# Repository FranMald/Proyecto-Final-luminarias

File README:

Prueba de archivo readme sadfasdasd

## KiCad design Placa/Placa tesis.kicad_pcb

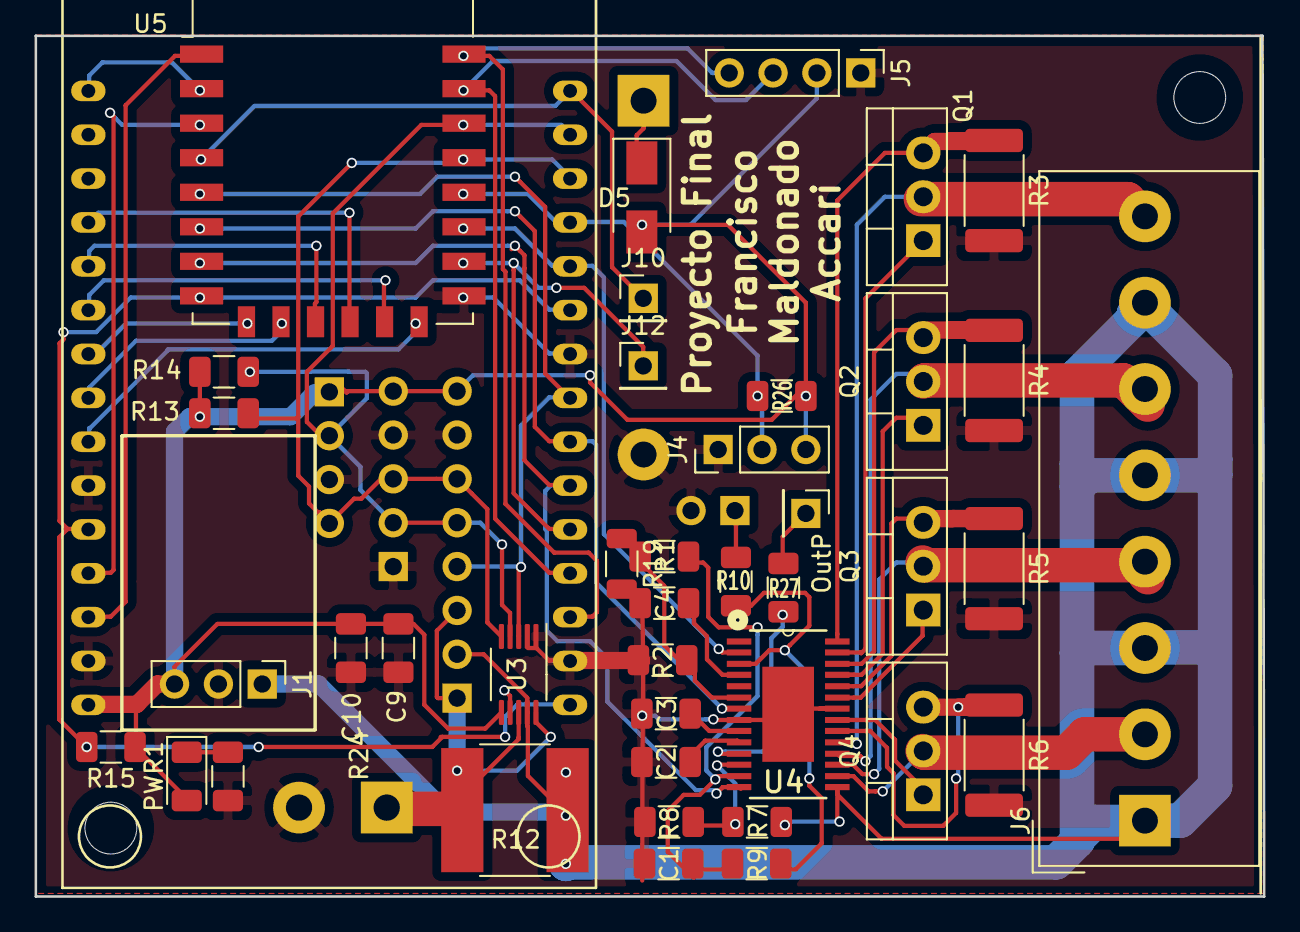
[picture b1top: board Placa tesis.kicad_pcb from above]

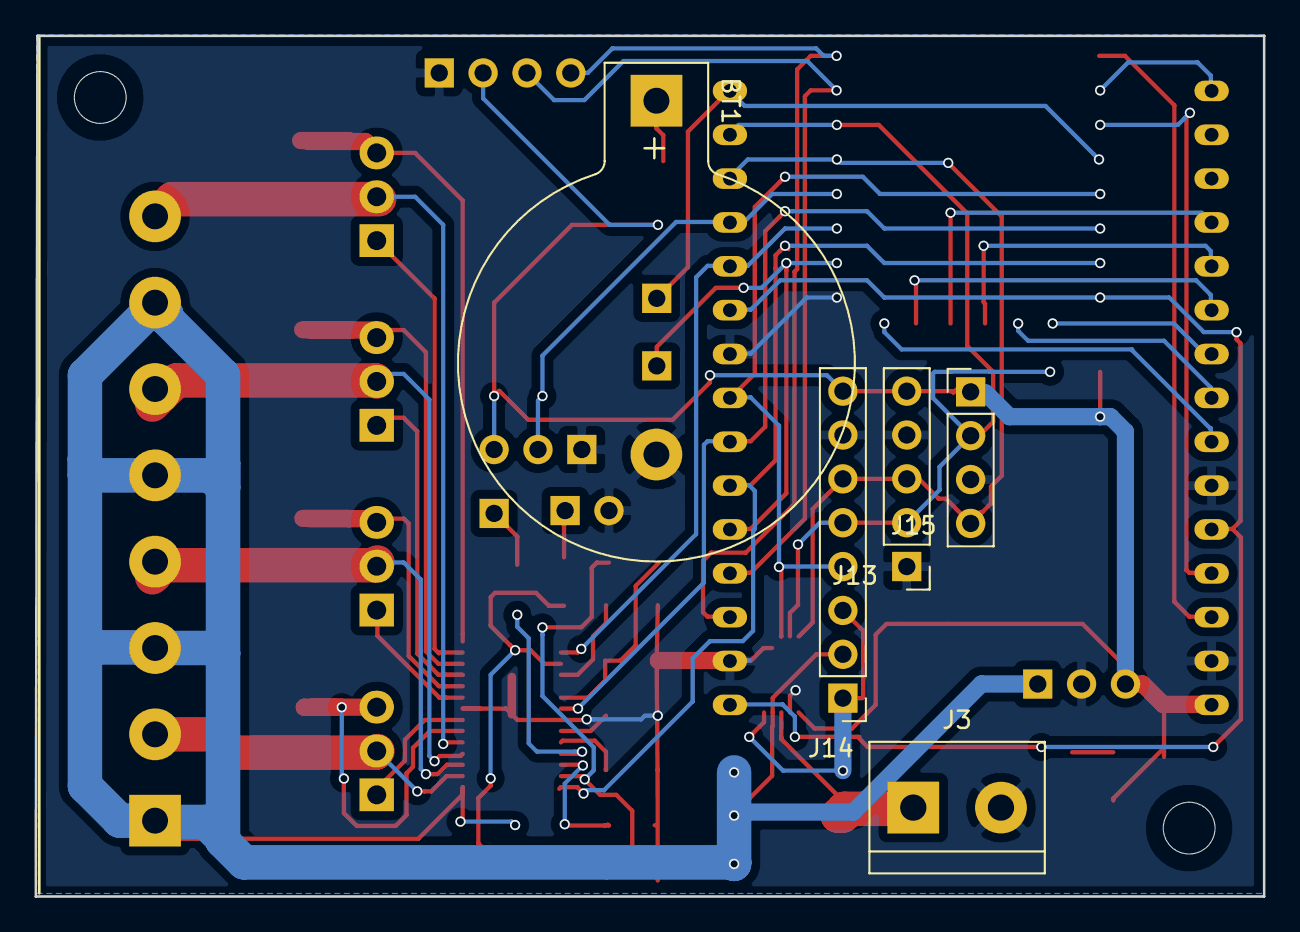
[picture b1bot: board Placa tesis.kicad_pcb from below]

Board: 2 copper layers, 71.1 x 49.9 mm, 47 parts (5 on the bottom side), 48 nets.

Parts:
BT1: Battery_Cell; BatteryHolder_Keystone_103_1x20mm
C1, C2, C4: 1u; C_1206_3216Metric
C3: 2.2n; C_1206_3216Metric
C9: 4.7u; C_1206_3216Metric
C10: 100n; C_1206_3216Metric
D5: DIODE; D_SMA
J1: OKI-78SR; Pin_Header_Straight_1x03_Pitch2.54mm
J3: FUENTE; TerminalBlock_bornier-2_P5.08mm
J4: DHT11; PinHeader_1x03_P2.54mm_Vertical
J5: COMM; PinHeader_1x04_P2.54mm_Vertical
J6: Conn_01x08; Altech_AK300_1x08_P5.00mm_45-Degree
J10, J12: Conn_01x01; PinHeader_1x01_P2.54mm_Vertical
J13: BH1750; PinHeader_1x05_P2.54mm_Vertical
J14: INA226; PinHeader_1x08_P2.54mm_Vertical
J15: Conn_01x04; PinHeader_1x04_P2.54mm_Vertical
OutP: Pin_Header_Straight_1x01_Pitch2.54mm
PWR1: LED; LED_1206_3216Metric
Q1, Q2, Q3, Q4: Q_NMOS_GDS; TO-220-3_Vertical
R1, R7, R19: 10k; R_1206_3216Metric
R2, R26: 4.7k; R_1206_3216Metric
R3, R4, R5, R6: 0.2; R_2512_6332Metric
R8: 1.5k; R_1206_3216Metric
R9, R10, R27: R; R_1206_3216Metric
R12: 270; R_2816
R13, R14: 10K; R_1206_3216Metric
R15: 0.001; R_1206_3216Metric
R24: 270; R_1206_3216Metric
TH1: Thermistor_NTC; Pin_Header_Angled_1x02_Pitch2.54mm
U2: Nodemcuv_3; DIP-30_1098_ELL
U3: INA226; VSSOP-10_3x3mm_P0.5mm
U4: LM3464AMH_NOPB; SOP65P640X110-29N
U5: ESP-12E

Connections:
A0: U2.1, U5.2
ALARM: J14.4, U2.23, U3.3, U5.5
D0: J10.1, U2.30, U5.4
D1: J13.2, J14.5, J15.2, R14.1, U2.29, U3.4, U5.20
D2: J13.3, J14.6, J15.4, R13.1, U2.28, U3.5, U5.19
D3: J4.2, R26.2, U2.27, U5.18
D4: U2.26, U4.2, U5.17
D6: U2.22, U4.7, U5.6
D7: U2.21, U4.14, U5.7
D8: J12.1, R19.1, U2.20, U5.16
DR1: J6.8, Q1.2, U4.19
DR2: J6.6, Q2.2, U4.18
DR3: J6.4, Q3.2, U4.17
DR4: J6.2, Q4.2, U4.16
EN_esp: U2.12, U5.3
GD1: Q1.1, U4.27
GD2: Q2.1, U4.25
GD3: Q3.1, U4.23
GD4: Q4.1, U4.21
GND: BT1.2, C1.2, C2.2, C3.2, C4.2, C9.2, C10.2, J1.2, J3.2, J4.1, J5.1, J13.1, J13.4, J14.7, J15.3, R2.2, R3.2, R4.2, R5.2, R6.2, R8.2, R19.2, R24.1, TH1.2, U2.10, U2.14, U2.17, U2.24, U3.1, U3.2, U3.7, U4.8, U4.22, U5.15
unnamed: BT1.1, D5.1
unnamed: C2.1, U4.10
unnamed: C3.1, U4.9
unnamed: C4.1, U4.4
unnamed: PWR1.1, R24.2
unnamed: R1.2, R2.1, U4.6
unnamed: R7.2, R8.1, U4.12
unnamed: R9.2, R10.1, U4.3
unnamed: R27.2, U4.11
OutP: OutP.1, R27.1
RST_esp: U2.13, U5.1
RX: J5.3, U2.19, U5.21
S0: U2.8, U5.10
S1: U2.6, U5.13
S2: U2.5, U5.11
S3: U2.4, U5.12
SC: U2.7, U5.9
SE1: Q1.3, R3.1, U4.28
SE2: Q2.3, R4.1, U4.26
SE3: Q3.3, R5.1, U4.24
SE4: Q4.3, R6.1, U4.20
SK: U2.9, U5.14
THR: R10.2, TH1.1
TX: J5.4, U2.18, U5.22
V5: C9.1, C10.1, D5.2, J1.3, J4.3, J5.2, J13.5, J14.8, J15.1, PWR1.2, R13.2, R14.2, R15.1, R15.2, R26.1, U2.11, U2.15, U2.16, U2.25, U3.6, U5.8
VccLED: C1.1, R1.1, R9.1, U4.13
Vin: J1.1, J6.1, J6.3, J6.5, J6.7, J14.2, R7.1, R12.1, U3.9, U4.15
VinS: J3.1, J14.1, J14.3, R12.2, U3.8, U3.10

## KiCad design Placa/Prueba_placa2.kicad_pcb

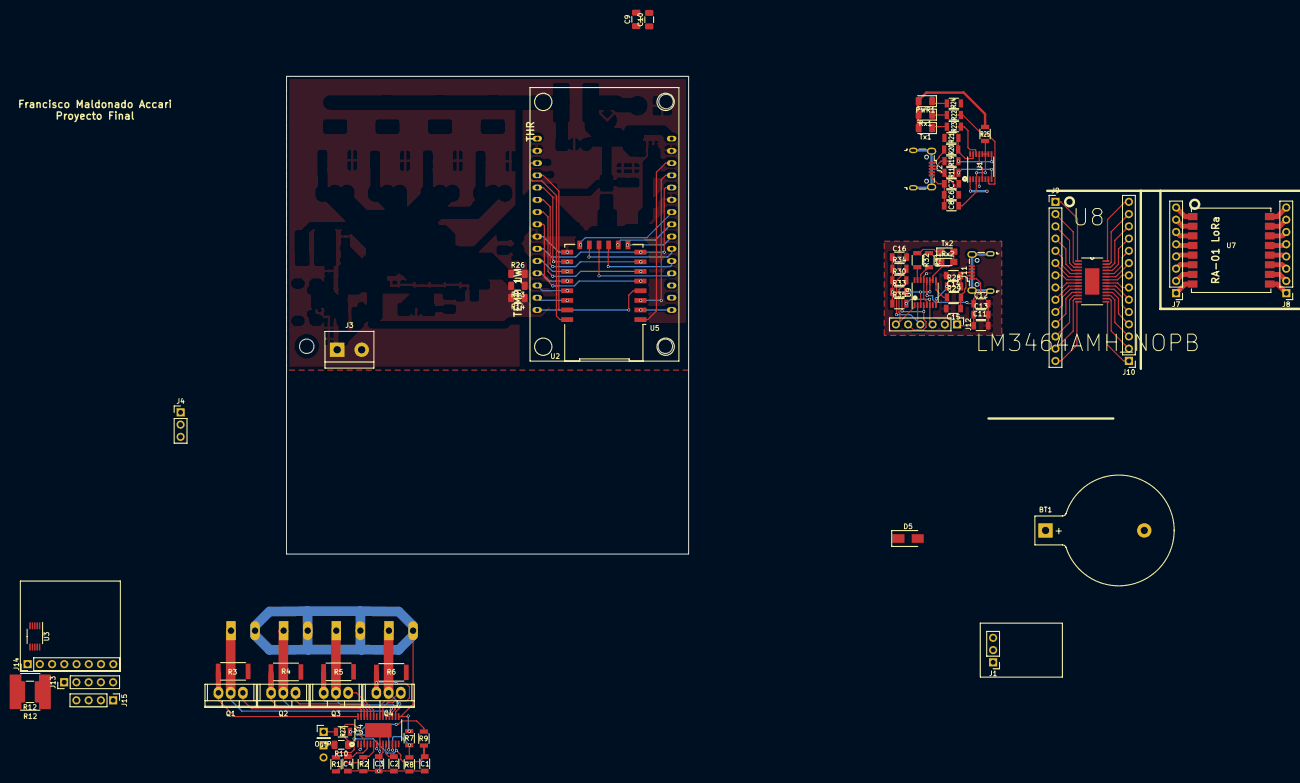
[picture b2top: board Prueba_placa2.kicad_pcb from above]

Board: 2 copper layers, 85 parts (0 on the bottom side), 119 nets.

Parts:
BT1: Battery_Cell; BatteryHolder_Keystone_103_1x20mm
C1, C13: 10n; C_1206
C2, C3, C4: C; C_1206
C6, C7, C14, C15: 47p; C_1206
C8, C12, C16: 100n; C_1206
C9: 4.7u; C_1206_3216Metric
C10: 100n; C_1206_3216Metric
C11: 4.7u; C_1206
D1, D2, D4: LED; TerminalBlock_Altech_AK300-2_P5.00mm
D3: LED; TerminalBlock_Altech_AK300-2_P5.00mmnosilk
D5: DIODE; D_SMA
J1: Conn_01x03; Pin_Header_Straight_1x03_Pitch2.54mm
J2, J11: USB_B_Micro; USB_Micro-B_Wuerth-629105150521
J3: Conn_01x02; TerminalBlock_bornier-2_P5.08mm
J4: Conn_01x03; PinHeader_1x03_P2.54mm_Vertical
J7, J8: Conn_01x08; Pin_Header_Straight_1x08_Pitch2.54mm
J9, J10: Conn_01x14; Pin_Header_Straight_1x14_Pitch2.54mm
J12: Conn_01x06; Pin_Header_Straight_1x06_Pitch2.54mm
J13: Conn_01x05; PinHeader_1x05_P2.54mm_Vertical
J14: Conn_01x08; PinHeader_1x08_P2.54mm_Vertical
J15: Conn_01x04; PinHeader_1x04_P2.54mm_Vertical
OutP: Pin_Header_Straight_1x01_Pitch2.54mm
PWR1: LED; LED_1206_3216Metric
Q1, Q2, Q3, Q4: Q_NMOS_GDS; TO-220
R1, R2, R7, R8, R9, R27: R; R_1206
R3, R4, R5, R6: 0.2; R_2512
R10: R; R_1206_3216Metric
R11, R19, R28, R29: 27; R_1206
R12: 7.5m; R_2816
R12#2: 270; R_2816_7142Metric
R13, R14: 10K; R_1206_3216Metric
R20: 4.7k; R_1206
R21: 10k; R_1206
R22, R23, R24, R31, R32: 270; R_1206
R25: .1; R_1206
R26: 4.7k; R_1206_3216Metric
R30, R33, R34, R35: 10K; R_1206
Rx1: LED; LED_1206_3216Metric
Rx2: LED; LED_0805_HandSoldering
TH1: Thermistor_NTC; Pin_Header_Angled_1x02_Pitch2.54mm
Tx1: LED; LED_1206_3216Metric
Tx2: LED; LED_0805_HandSoldering
U1, U9: FT230XS; SSOP-16_3.9x4.9mm_Pitch0.635mm
U2: Nodemcuv_3; DIP-30_1098_ELL
U3: INA226; VSSOP-10_3x3mm_P0.5mm
U4, U8: LM3464AMH_NOPB; SOP65P640X110-29N
U5: ESP-12E
U7: Ra-01-LoRa; Ai-Thinker-Ra-01-LoRa

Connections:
A0: U2.1, U5.2
ALARM: J14.4, U2.23, U3.3, U5.5
D0: U2.30, U5.4
D1: J13.2, J14.5, J15.2, R14.1, U2.29, U3.4, U5.20
D2: J13.3, J14.6, J15.4, R13.1, U2.28, U3.5, U5.19
D3: J4.2, R26.2, U2.27, U5.18
D4: U2.26, U4.2, U5.17
D6: U2.22, U4.7, U5.6
D7: U2.21, U4.14, U5.7
D8: U2.20, U5.16
DR1: D1.1, Q1.2, U4.19
DR2: D2.1, Q2.2, U4.18
DR3: D3.1, Q3.2, U4.17
DR4: D4.1, Q4.2, U4.16
EN_esp: U2.12, U5.3
GD1: Q1.1, U4.27
GD2: Q2.1, U4.25
GD3: Q3.1, U4.23
GD4: Q4.1, U4.21
GND: BT1.2, C1.2, C2.2, C3.2, C4.2, C6.2, C7.2, C8.2, C9.2, C10.2, J1.2, J2.5, J3.1, J4.1, J13.1, J13.4, J14.7, J15.3, R2.2, R3.2, R4.2, R5.2, R6.2, R8.2, R21.2, R24.1, TH1.2, U1.5, U1.13, U2.10, U2.14, U2.17, U2.24, U3.1, U3.2, U3.7, U4.8, U4.22, U5.15
GND2: C11.2, C12.2, C13.2, C14.2, C15.2, C16.2, J11.5, J12.2, U9.5, U9.13
unnamed: BT1.1, D5.1
unnamed: C2.1, U4.10
unnamed: C3.1, U4.9
unnamed: C4.1, U4.4
unnamed: C6.1, J2.3, R11.2
unnamed: C7.1, J2.2, R19.2
unnamed: C8.1, R25.1, U1.3, U1.10, U1.11, U1.12
unnamed: C11.1, C12.1, C13.1, J11.1, J12.1, U9.12
unnamed: C14.1, J11.3, R28.2
unnamed: C15.1, J11.2, R29.2
unnamed: C16.1, R30.1, R33.1, R34.1, R35.1, Rx2.2, Tx2.2, U9.3, U9.10, U9.11
unnamed: J2.1, R20.1
unnamed: J7.1, U7.8
unnamed: J7.2, U7.7
unnamed: J7.3, U7.6
unnamed: J7.4, U7.5
unnamed: J7.5, U7.4
unnamed: J7.6, U7.3
unnamed: J7.7, U7.2
unnamed: J7.8, U7.1
unnamed: J8.1, U7.9
unnamed: J8.2, U7.10
unnamed: J8.3, U7.11
unnamed: J8.4, U7.12
unnamed: J8.5, U7.13
unnamed: J8.6, U7.14
unnamed: J8.7, U7.15
unnamed: J8.8, U7.16
unnamed: J9.1, U8.1
unnamed: J9.2, U8.2
unnamed: J9.3, U8.3
unnamed: J9.4, U8.4
unnamed: J9.5, U8.5
unnamed: J9.6, U8.6
unnamed: J9.7, U8.7
unnamed: J9.8, U8.8
unnamed: J9.9, U8.9
unnamed: J9.10, U8.10
unnamed: J9.11, U8.11
unnamed: J9.12, U8.12
unnamed: J9.13, U8.13
unnamed: J9.14, U8.14
unnamed: J10.1, U8.15
unnamed: J10.2, U8.16
unnamed: J10.3, U8.17
unnamed: J10.4, U8.18
unnamed: J10.5, U8.19
unnamed: J10.6, U8.20
unnamed: J10.7, U8.21
unnamed: J10.8, U8.22
unnamed: J10.9, U8.23
unnamed: J10.10, U8.24
unnamed: J10.11, U8.25
unnamed: J10.12, U8.26
unnamed: J10.13, U8.27
unnamed: J10.14, U8.28
unnamed: J12.3, R35.2, U9.6
unnamed: J12.4, R34.2, U9.2
unnamed: J12.5, R33.2, U9.4
unnamed: J12.6, R30.2, U9.1
unnamed: PWR1.1, R24.2
unnamed: R1.2, R2.1, U4.6
unnamed: R7.2, R8.1, U4.12
unnamed: R9.2, R10.1, U4.3
unnamed: R10.2, TH1.1
unnamed: R11.1, U1.8
unnamed: R19.1, U1.9
unnamed: R20.2, R21.1, U1.15
unnamed: R22.1, Rx1.1
unnamed: R22.2, U1.7
unnamed: R23.1, Tx1.1
unnamed: R23.2, U1.14
unnamed: R27.2, U4.11
unnamed: R28.1, U9.8
unnamed: R29.1, U9.9
unnamed: R31.1, Rx2.1
unnamed: R31.2, U9.14
unnamed: R32.1, Tx2.1
unnamed: R32.2, U9.15
unnamed: U2.11, U2.16, U2.25, U5.8
OutP: OutP.1, R27.1
RST_esp: U2.13, U5.1
RX: U1.1, U2.19, U5.21
S0: U2.8, U5.10
S1: U2.6, U5.13
S2: U2.5, U5.11
S3: U2.4, U5.12
SC: U2.7, U5.9
SE1: Q1.3, R3.1, U4.28
SE2: Q2.3, R4.1, U4.26
SE3: Q3.3, R5.1, U4.24
SE4: Q4.3, R6.1, U4.20
SK: U2.9, U5.14
TX: U1.4, U2.18, U5.22
V5: C9.1, C10.1, D5.2, J1.3, J4.3, J13.5, J14.8, J15.1, PWR1.2, R13.2, R14.2, R25.2, R26.1, Rx1.2, Tx1.2, U2.15, U3.6
VccLED: C1.1, R1.1, R9.1, U4.13
Vin: D1.2, D2.2, D3.2, D4.2, J1.1, J14.2, R7.1, R12.1, R12#2.1, U3.9, U4.15
VinS: J3.2, J14.1, J14.3, R12.2, R12#2.2, U3.8, U3.10

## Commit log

2020-10-28 Commit de prueba
2020-10-28 Commit de prueba 2
2020-10-28 seguimos probando
2020-10-28 ahora si!
2020-10-28 quitè el IDE
2020-10-28 mejor organizado
2020-10-28 readme con formato .md
2020-10-28 agregada la placa al repo
2020-10-28 limpieza de la carpeta de placa
2020-10-28 aplicación desactualizado
2020-10-28 agregada lectura de sensor de corriente
2021-05-16 actualicacion despes de mucho
2021-05-19 Webserver funcionando
2021-10-13 actualizacion
2021-10-13 prueba de script
2021-10-13 asdf
2021-10-13 Agregar Informe
2022-03-02 Agregado de aplicacion Godot
2022-03-08 actualuzacion informe
2022-03-09 prueba comit doble
2022-03-09 Gauges en aplicacion Godot
2022-03-09 gauges en godot
2022-03-09 gauges instalados godot
2022-03-15 gauges
2022-03-22 prueba request y provisioning
2022-03-23 Request y comit funcionando
2022-03-25 provisioning y configuracion por request integrado al progrma principal
2022-03-25 archivos de configuracion
2022-03-25 codigo limpio
2022-04-07 separado en escenas
2022-04-28 avance en informe
2022-05-11 diagrams de flujo
2022-05-12 avance en diagramas
2022-05-12 diagrama de flujo
2022-05-12 Diagramas de flujo
2022-05-17 diagrama de flujo terminado
2022-05-24 formato informe
2022-05-24 dfgds
2022-06-02 diagramas de flujo terminados
2022-06-26 Informe Teoria MQTT
2024-04-25 La venganza
